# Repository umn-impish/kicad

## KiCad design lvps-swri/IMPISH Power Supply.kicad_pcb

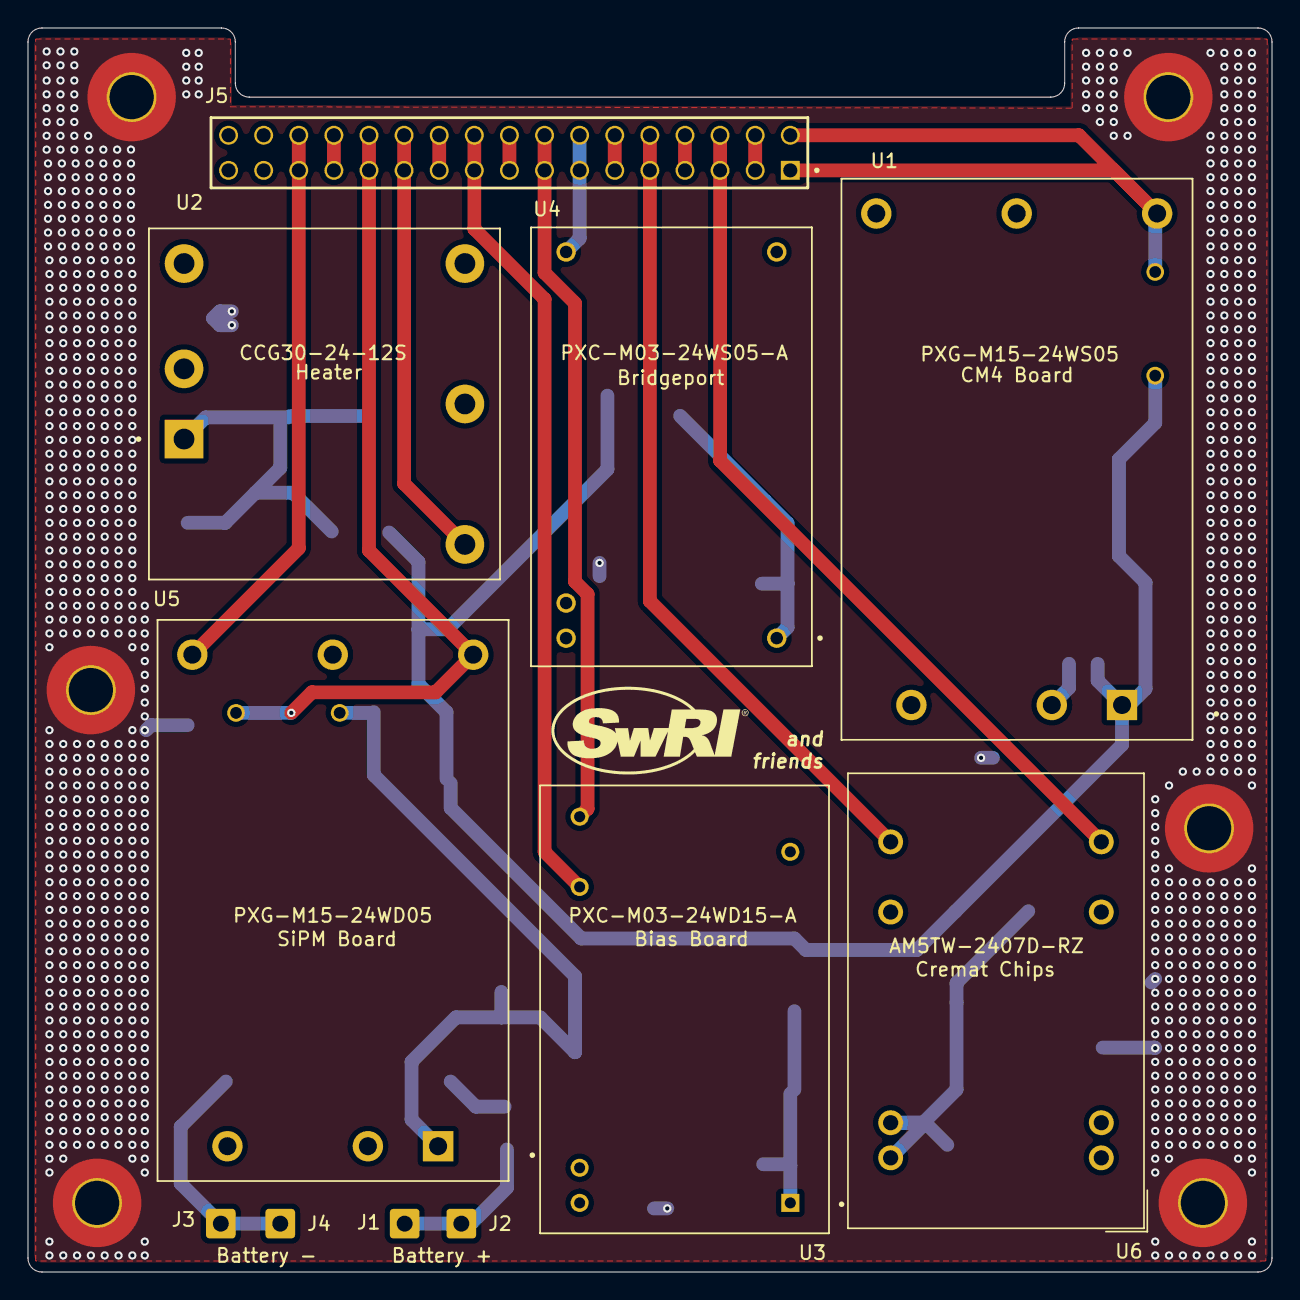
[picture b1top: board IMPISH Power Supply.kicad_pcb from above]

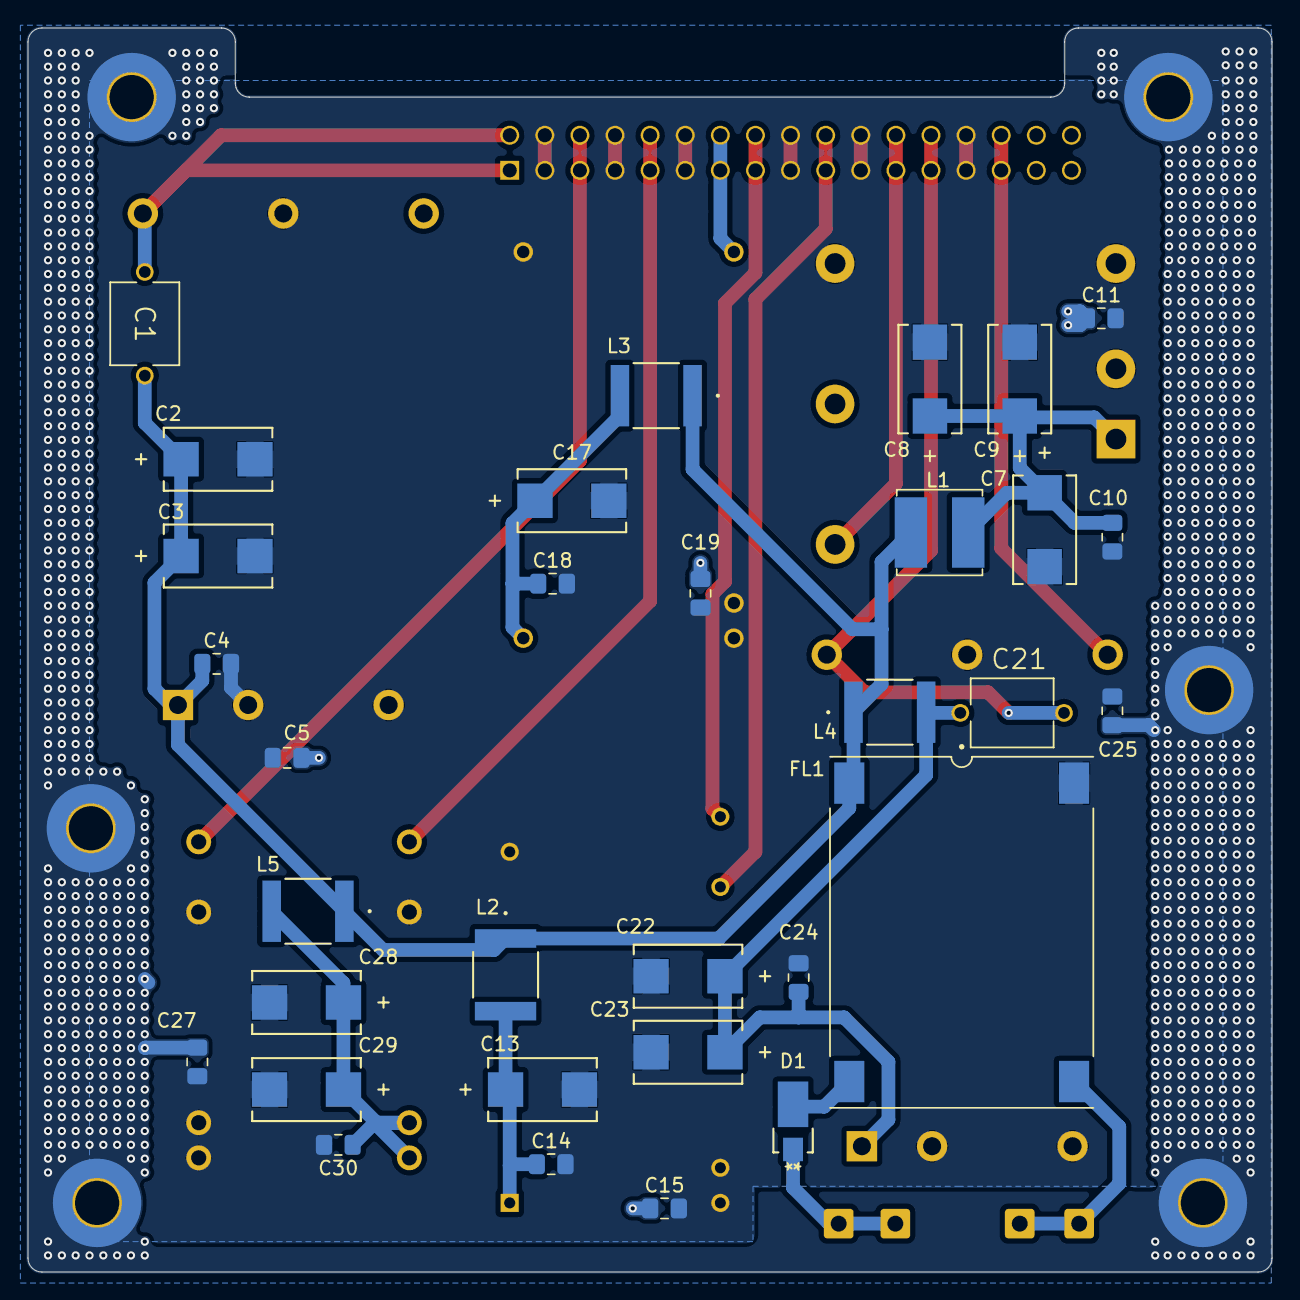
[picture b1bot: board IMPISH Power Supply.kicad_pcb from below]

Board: 2 copper layers, 90.0 x 90.0 mm, 49 parts (32 on the bottom side), 20 nets.

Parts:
C1, C21: 100pF; CAP_DE2B3SA101KN3AY02F
C2, C3, C22, C23: 10uF 50V; T495X106K050ATE300
C4, C5, C10, C11, C14, C15, C18, C19, C24, C25, C27, C30: .01uF; C_0805_2012Metric_Pad1.18x1.45mm_HandSolder
C7, C8, C9, C28, C29: 15uF 50V; T495X156K050ATE300
C13, C17: 4.7uF 50V; T495D475K050ATE275
D1: V8PAL50-M3/I; CR_DO-221BC_VIS
FL1: F4804A-RG; FIL_F4804A-RG
H1, H2, H3, H4, H5, H6: MountingHole_3.2mm_M3_Pad_TopBottom
J1, J2: Battery +; SolderWire-0.5sqmm_1x01_D0.9mm_OD2.1mm
J3, J4: Battery -; SolderWire-0.5sqmm_1x01_D0.9mm_OD2.1mm
J5: BCS-117-L-D-TE; SAMTEC_BCS-117-L-D-TE
L1: 15uH; L_Bourns_SRN6045TA
L2, L5: 220uH; SDS680R-105M
L3: 100uH; SDS680R-105M
L4: 10uH; SDS680R-105M
U1: PXG-M15-24WS05; CONV_PXG-M15-24WS05
U2: CCG30-24-12S; CONV_CCG30-24-12S
U3: PXC-M03-24WD15-A; CONV_PXC-M03-24WD15-A
U4: PXC-M03-24WS05-A; CONV_PXC-M03-24WS05-A
U5: PXG-M15-24WD05; CONV_PXG-M15-24WD05
U6: AM5TW-2407D-RZ; CONV_AM5TW-2407D-RZ

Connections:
Bias +15V: J5.19, J5.20, U3.15 (+VOUT)
Bias -15V: J5.15, J5.16, U3.13 (-VOUT)
Bridgeport +5V: J5.13, J5.14, U4.13 (+VOUT)
CHASSIS: C5.1, C11.1, C15.1, C19.1, C25.1, C27.1, H1.1, H2.1, H3.1, H4.1, H5.1, H6.1
CM4 +5V: C1.2, J5.01, J5.02, U1.4 (+VOUT)
Cremat +7.2V: J5.09, J5.10, U6.14 (+Vout)
Cremat -7.2V: J5.05, J5.06, U6.11 (-Vout)
GND: C2.2, C3.2, C4.2, C5.2, C7.2, C8.2, C9.2, C10.2, C11.2, C13.2, C14.2, C15.2, C17.2, C18.2, C19.2, C22.2, C23.2, C24.2, C25.2, C27.2, C28.2, C29.2, C30.2, FL1.-OUT, J5.03, J5.04, J5.07, J5.08, J5.11, J5.12, J5.17, J5.18, J5.21, J5.22, J5.27, J5.28, U1.2 (-VIN), U1.3 (REMOTE_ON/OFF), U1.5 (-VOUT), U2.2 (-VIN), U2.3 (RC), U2.6 (-VOUT), U3.11 (COM), U3.23 (-VIN), U3.24 (-VIN__1), U4.12 (-VOUT), U4.23 (-VIN), U4.24 (-VIN__1), U5.2 (-VIN), U5.3 (REMOTE_ON/OFF), U5.5 (COMMON), U6.2 (-Vin), U6.3 (-Vin), U6.9 (Com), U6.16 (Com)
Heater 12V: J5.23, J5.24, U2.4 (+VOUT)
unnamed: C28.1, C29.1, C30.1, L5.2, U6.22 (+Vin), U6.23 (+Vin)
unnamed: D1.2 (A), J1.1, J2.1
unnamed: D1.1 (K), FL1.+IN
unnamed: FL1.-IN, J3.1, J4.1
unnamed: C1.1, C2.1, C3.1, C4.1, FL1.+OUT, L1.1, L2.1, L3.1, L4.1, L5.1, U1.1 (+VIN)
unnamed: C7.1, C8.1, C9.1, C10.1, L1.2, U2.1 (+VIN)
unnamed: C13.1, C14.1, L2.2, U3.1 (+VIN)
unnamed: C17.1, C18.1, L3.2, U4.1 (+VIN)
unnamed: C21.1, C22.1, C23.1, C24.1, L4.2, U5.1 (+VIN)
SiPM +5V: C21.2, J5.25, J5.26, U5.4 (+VOUT)
SiPM -5V: J5.29, J5.30, U5.6 (-VOUT)

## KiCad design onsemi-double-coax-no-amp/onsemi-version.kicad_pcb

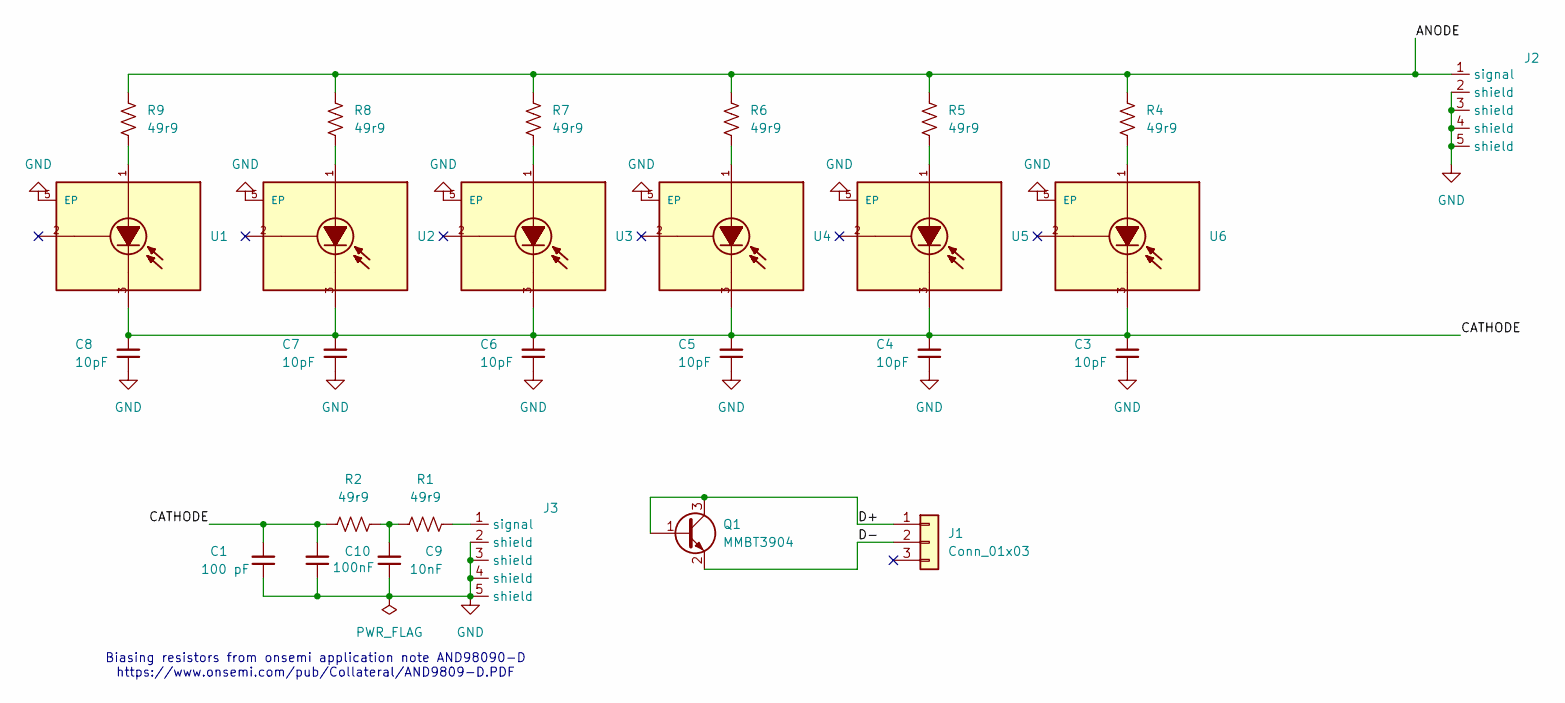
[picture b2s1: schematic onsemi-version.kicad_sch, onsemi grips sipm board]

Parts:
C1: 100 pF; C_0805_2012Metric
C3, C4, C5, C6, C7, C8: 10pF; C_0805_2012Metric
C9: 10nF; C_0805_2012Metric
C10: 100nF; C_0805_2012Metric
J1: Conn_01x03; Harwin_LTek-Male_03_P2.00mm_Vertical
J2, J3: CONN_73415-1472_MOL
Q1: MMBT3904; SOT-23
R1, R2, R4, R5, R6, R7, R8, R9: 49r9; R_0402_1005Metric
U1, U2, U3, U4, U5, U6: MICROFC-60035-SMT-TR1; XDCR_MICROFC-60035-SMT-TR1; PARTREV 31 JUL 2018

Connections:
/ANODE: J2.1 (signal), R4.2, R5.2, R6.2, R7.2, R8.2, R9.2
/CATHODE: C1.2, C3.2, C4.2, C5.2, C6.2, C7.2, C8.2, C10.2, R2.1, U1.3, U2.3, U3.3, U4.3, U5.3, U6.3
/D+: J1.1, Q1.1 (B), Q1.3 (C)
/D-: J1.2, Q1.2 (E)
GND: C1.1, C3.1, C4.1, C5.1, C6.1, C7.1, C8.1, C9.1, C10.1, J2.2 (shield), J2.3 (shield), J2.4 (shield), J2.5 (shield), J3.2 (shield), J3.3 (shield), J3.4 (shield), J3.5 (shield), U1.5 (EP), U2.5 (EP), U3.5 (EP), U4.5 (EP), U5.5 (EP), U6.5 (EP)
unnamed: C9.2, R1.1, R2.2
unnamed: J3.1 (signal), R1.2
unnamed: R4.1, U6.1
unnamed: R5.1, U5.1
unnamed: R6.1, U4.1
unnamed: R7.1, U3.1
unnamed: R8.1, U2.1
unnamed: R9.1, U1.1

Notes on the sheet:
Biasing resistors from onsemi application note AND98090-D https://www.onsemi.com/pub/Collateral/AND9809-D.PDF

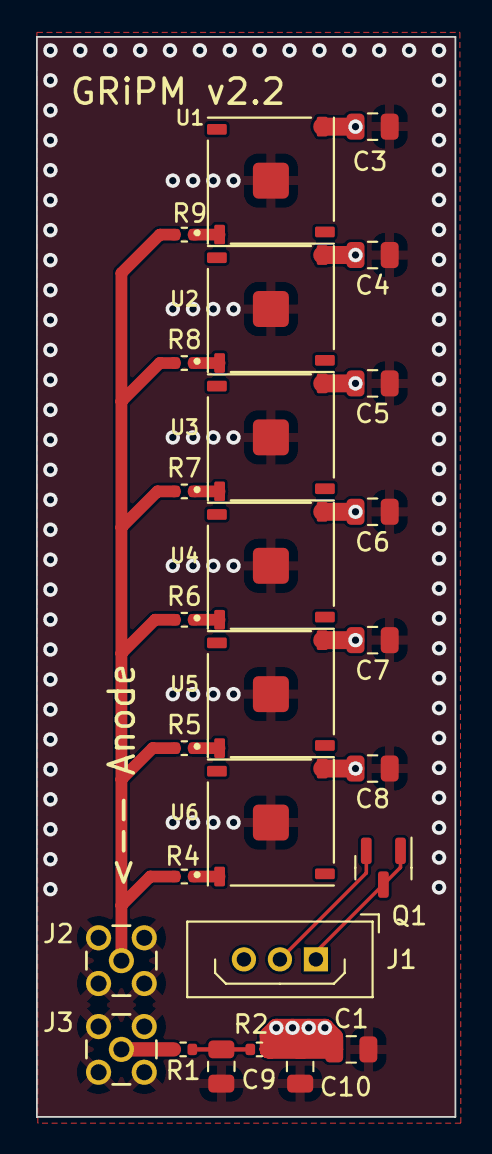
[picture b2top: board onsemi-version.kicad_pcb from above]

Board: 2 copper layers, 23.2 x 60.0 mm, 27 parts (0 on the bottom side), 13 nets.

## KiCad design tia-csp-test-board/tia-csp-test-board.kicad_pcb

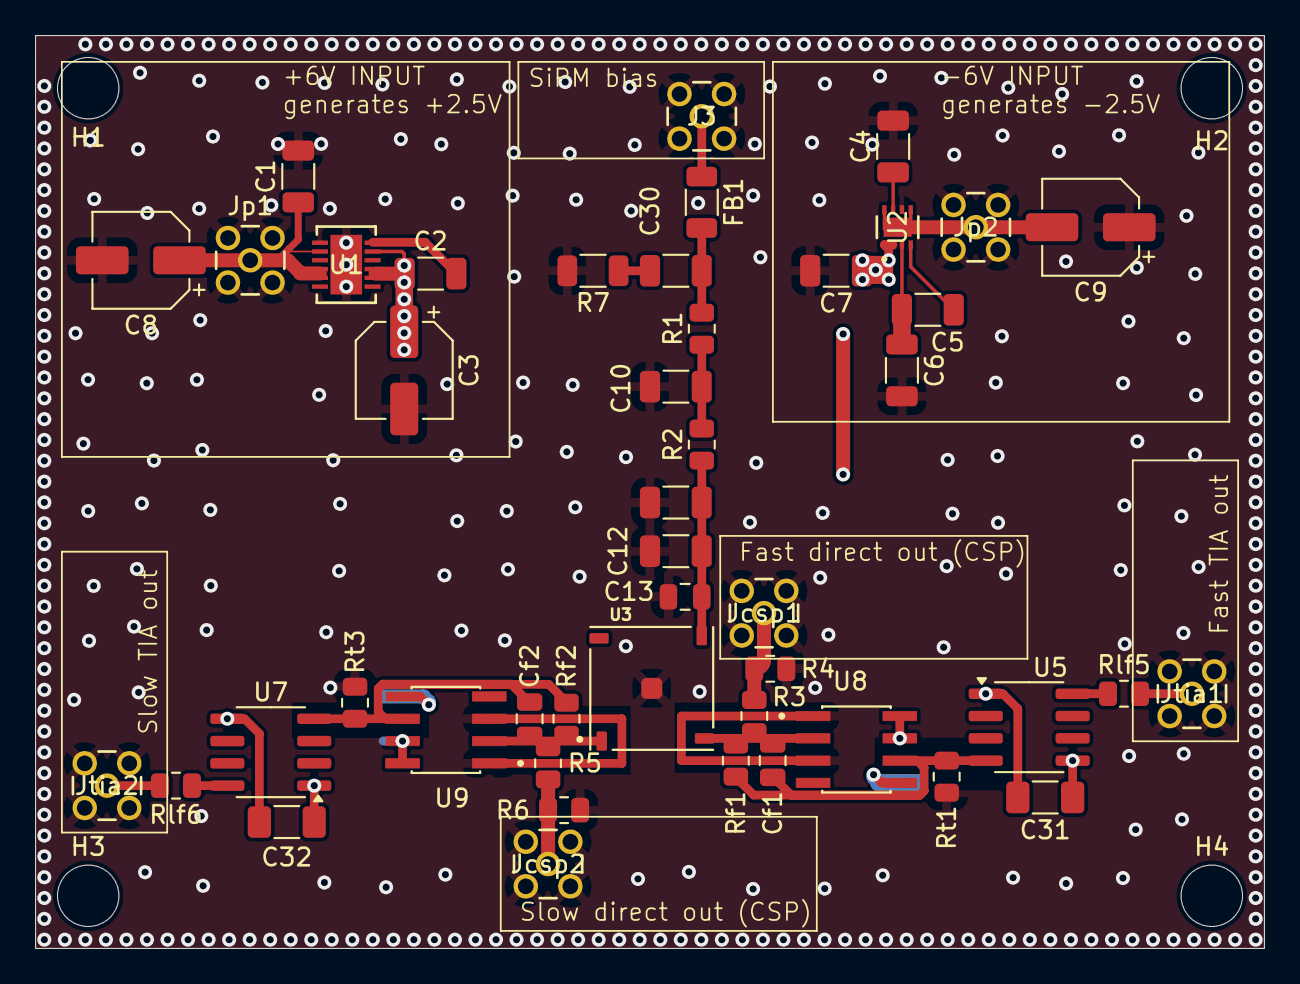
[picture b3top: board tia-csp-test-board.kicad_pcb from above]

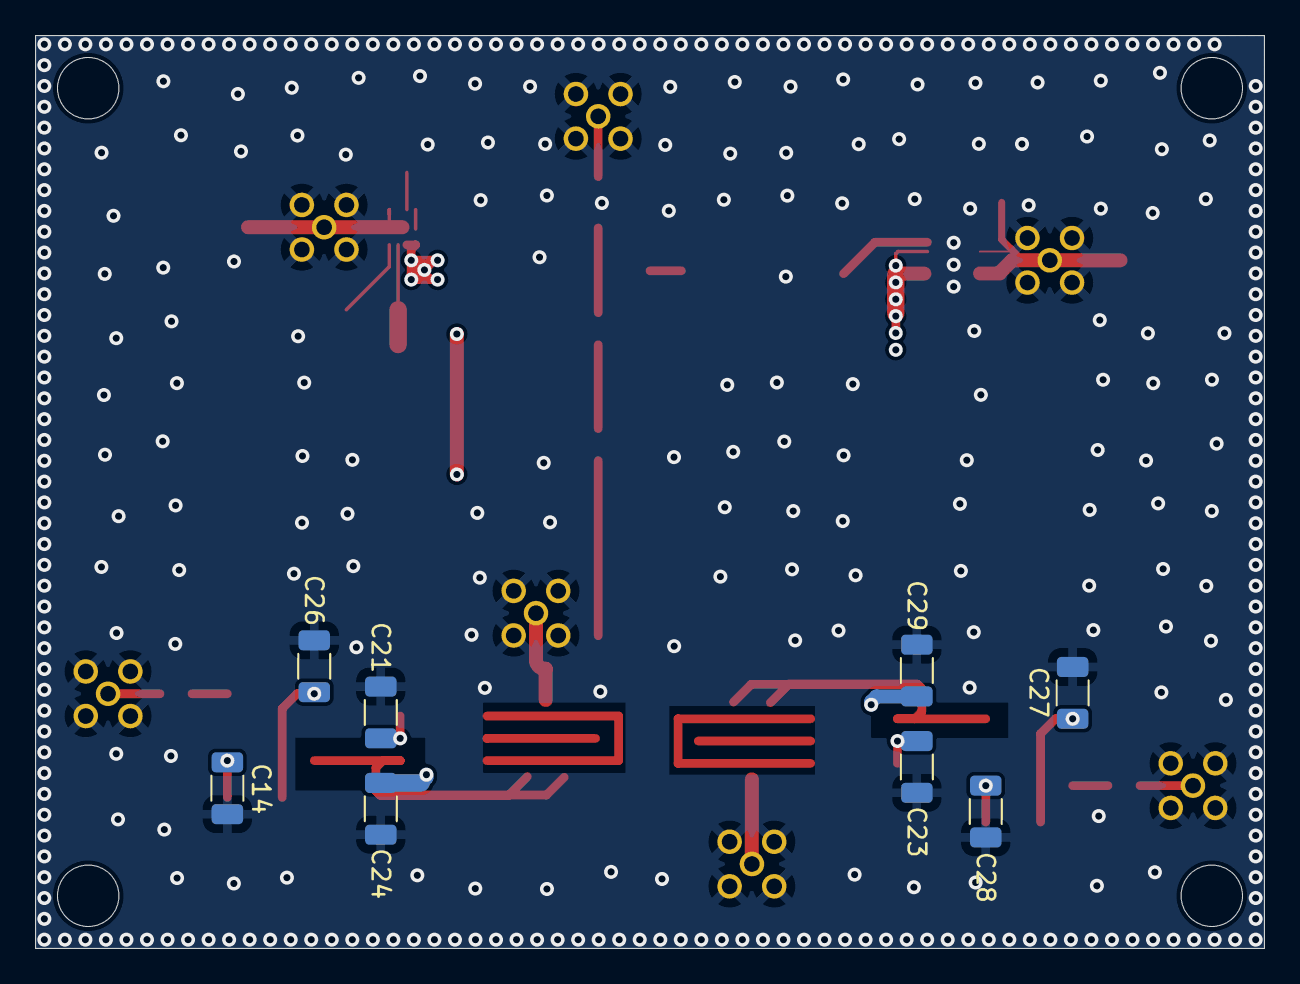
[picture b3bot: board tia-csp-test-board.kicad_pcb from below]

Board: 4 copper layers, 70.0 x 52.0 mm, 58 parts (8 on the bottom side), 24 nets.

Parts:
C1, C2, C4, C6, C30: 1u; C_1206_3216Metric
C3, C8, C9: 10u; CP_Elec_5x4.5
C5, C10, C12: 10n; C_1206_3216Metric
C7: 4.7u; C_1206_3216Metric
C11: 100n; C_1206_3216Metric
C13: 10p; C_0805_2012Metric
C14, C21, C23, C24, C26, C27, C28, C29: 0.1u; C_1206_3216Metric
C31, C32: 10n; C_1206_3216Metric_Pad1.33x1.80mm_HandSolder
Cf1, Cf2: var; C_0805_2012Metric
FB1: 620@1M; R_1206_3216Metric
H1, H2, H3, H4: MountingHole; MountingHole_3.5mm
J3: 734151472; CONN_73415-1472_MOL
Jcsp1, Jcsp2: 734151472; CONN_73415-1472_MOL
Jp1, Jp2: 734151472; CONN_73415-1472_MOL
Jtia1, Jtia2: 734151472; CONN_73415-1472_MOL
R1, R2, R4, R6: 50; R_0805_2012Metric
R3, R5: 0; R_0805_2012Metric
R7: 2; R_1206_3216Metric
Rf1, Rf2: var; R_0805_2012Metric
Rlf5, Rlf6: 50; R_0805_2012Metric
Rt1, Rt3: 10k; R_0805_2012Metric
U1: LT1763CDE-2.5-PBF; LT1763
U2: ADP7185ACPZN2.5-R7; ADP7185
U3: MICROFC-60035-SMT-TR1; XDCR_MICROFC-60035-SMT-TR1
U5, U7: BUF602xD; SOIC-8_3.9x4.9mm_P1.27mm
U8, U9: LTC6268HS8-10_PBF; SOIC127P599X175-8N

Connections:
+2V5: C2.1, C3.1, C21.2, C23.2, U1.2 (OUT), U1.3 (OUT), U1.5 (SENSE/ADJ), U8.7 (V+), U8.8 (~SHDN), U9.7 (V+), U9.8 (~SHDN)
+6V: C1.1, C8.1, C26.2, C28.2, C31.2, C32.2, Jp1.1 (SIGNAL), U1.8 (*SHDN), U1.10 (IN), U1.11 (IN), U5.1 (V+), U7.1 (V+)
-2V5: C7.1, C24.2, C29.2, U2.1 (VOUT), U2.2 (SENSE), U8.5 (V-), U9.5 (V-)
-6V: C9.2, C14.2, C27.2, C31.1, C32.1, Jp2.1 (SIGNAL), U2.5 (EN), U2.8 (VIN), U2.9 (EPAD), U5.5 (V-), U7.5 (V-)
/Bias filter/bias_filtered: C11.1, C12.1, C13.1, R2.1, U3.3
/Bias filter/bias_raw: FB1.1, J3.1 (SIGNAL)
/SiPM/anode (slow output): Cf2.2, R5.1, Rf2.2, U3.1, U9.2 (-IN)
/SiPM/fast output: Cf1.2, R3.2, Rf1.2, U3.2, U8.2 (-IN)
/driven TIA1/amp_out: Jtia2.1 (SIGNAL), Rlf6.2
/driven TIA/amp_out: Jtia1.1 (SIGNAL), Rlf5.2
GND: C1.2, C3.2, C4.2, C6.2, C7.2, C8.2, C9.1, C10.2, C11.2, C12.2, C13.2, C14.1, C21.1, C23.1, C24.1, C26.1, C27.1, C28.1, C29.1, J3.2 (GND), J3.3 (GND), J3.4 (GND), J3.5 (GND), Jcsp1.2 (GND), Jcsp1.3 (GND), Jcsp1.4 (GND), Jcsp1.5 (GND), Jcsp2.2 (GND), Jcsp2.3 (GND), Jcsp2.4 (GND), Jcsp2.5 (GND), Jp1.2 (GND), Jp1.3 (GND), Jp1.4 (GND), Jp1.5 (GND), Jp2.2 (GND), Jp2.3 (GND), Jp2.4 (GND), Jp2.5 (GND), Jtia1.2 (GND), Jtia1.3 (GND), Jtia1.4 (GND), Jtia1.5 (GND), Jtia2.2 (GND), Jtia2.3 (GND), Jtia2.4 (GND), Jtia2.5 (GND), R4.2, R6.2, R7.2, Rt1.2, Rt3.2, U1.7 (GND), U1.13 (EPAD), U2.6 (GND), U3.5 (EP), U8.1 (Guard_GND), U8.3 (+IN), U9.1 (Guard_GND), U9.3 (+IN)
unnamed: C10.1, R1.1, R2.2
unnamed: C30.1, FB1.2, R1.2
unnamed: C30.2, R7.1
unnamed: Jcsp1.1 (SIGNAL), R3.1, R4.1
unnamed: Jcsp2.1 (SIGNAL), R5.2, R6.1
unnamed: Rlf5.1, U5.8
unnamed: Rlf6.1, U7.8
unnamed: C2.2, U1.6 (BYP)
unnamed: C5.1, C6.1, U2.3 (VA)
unnamed: C5.2, U2.4 (VAFB)
unnamed: C4.1, U2.7 (VREG)
unnamed: Cf1.1, Rf1.1, Rt1.1, U5.4 (IN), U8.6 (OUT)
unnamed: Cf2.1, Rf2.1, Rt3.1, U7.4 (IN), U9.6 (OUT)

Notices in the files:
parts and their libraries:
Copyright 2016 Accelerated Designs. All rights reserved.
